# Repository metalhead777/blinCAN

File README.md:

# blinCAN
A 24 channel LED driver module with CAN bus interface and Arduino-compatible microcontroller. 

*blinCAN v0.1 2018 top*

*blinCAN v0.1 2018 bottom*

## Function description

The blinCAN is based on a multi-channel power LED driver module developed for the [Desert Eyes project](http://deserteyes.net/). 
It is matched to a small-scale construction prototype dome, which served to test construction and lighting patterns for the full-scale dome. 

This module is built around a TLC5947 PWM LED driver IC, which is connected to an ATmega328 microcontroller. 
For communication, a MCP2551 CAN transceiver and a MCP2515 CAN controller with SPI interface to the microcontroller are utilized. 
A FT232R USB to UART interface has been added to allow programming via USB, once a bootloader is flashed onto the microcontroller. 
For ambient air temperature sensing, a LM35 temperature sensor has been placed near the LED driver IC. 
A DIP switch is used to set a hardware-level address on each device, which also gets indicated by corresponding LEDs.
For easier connection of an already wired LED harness, 25-pin SUB-D connectors are used on the output. 

On the small-scale construction prototype dome, a Raspberry Pi with a CAN bus HAT was used as a host to centrally generate and send lighting patterns to six blinCAN modules via the CAN bus. 
Each blinCAN module had a unique address within the CAN bus, and every LED on the dome was purposely connected to a predefined module output. 
This way, every LED on the dome's shell was distinctly addressable in 3D space. 
An underlying look-up-table in the host's software was used to map each pattern lighting point to an LED. 

### Current stage of development
Currently the blinCAN is in early development state in version 0.1. 
This means, that the hardware is tested and working on a small prototype scale production. 
Long-term testing (temperature, vibration, EMI) has not been performed yet. 
In this state the blinCAN is fit to be used for embedded systems and small-scale lighting projects. 
Any large-scale production is not encouraged, since additional optimization in the hardware layout needs to be done for that. 

A few prototypes have been built and successfully tested prior to releasing this repository. 

### Device commissioning description

#### Device connection

#### Device power requirements

### Device programming

After assembly, the device can only be programmed using an ICSP in-circuit-programmer.
The connector with the reference **P103** serves as ICSP header.
The square pad is ICSP Pin 1 (MISO).

*P103 ICSP header pin connection*

The blinCAN firmware can be flashed directly to the ATmega328P-AU using an In-Series Programmer (ISP).
The reset-button needs to be pressed during microcontroller flashing

For editing the blinCAN firmware or testing any other Arduino-compatible code, the Arduino bootlader needs to be flashed first to the ATmega328P-AU used for the blinCAN.
A tutorial on flashing the Arduino bootloader can be found [here](https://www.arduino.cc/en/tutorial/arduinoISP).
Use the following settings under "Tools" in the Arduino IDE, if you use another Arduino as a flashing device (ISP):

| Parameter | Value          |
| --------- |:--------------:|
| Board     | "Arduino Nano" |
| Processor | "ATmega328P"   |

After flashing the Arduino bootloader, any further programming can be done using the USB type B connector (**P104**) on the blinCAN.

#### Windows

#### Linux

#### MacOS

#### List of successfully tested programming adaptors

### Device communication reference

#### Internal

#### External

#### Addressing scheme

## Currently known bugs and issues
- Reset-button needs to be pressed during microcontroller flashing
- The TLC5947 has a thermal pad, which makes it the only component not solderable by purely using a soldering iron. Using a heatgun to heat the pad from the bottom side, applying solder and then placing the TLC5947 onto it has been done successfully for the prototypes.

## Planned future changes and improvements
- Add Bill of Materials (BOM) for all non-KiCAD users
- Clean up trace routing around TLC5947
- Increase number of hardware address bits
- Change LED output voltage to board input voltage instead of fix 5 V
- Add polyfuse for input overcurrent protection
- Add additional mounting points for Raspberry Pi (host system)

## Open source hardware and software used in this project

### KiCAD

- [KiCAD website](http://kicad.org/)
- Licensed under [GPL Version 3](https://www.gnu.org/licenses/gpl-3.0.html)

### Arduino nano Rev. 3

- [Arduino website](https://www.arduino.cc/)
- [Arduino nano Rev. 3 schematic](https://arduino.cc/en/uploads/Main/Arduino_Nano-Rev3.2-SCH.pdf)
- Licensed under [CC BY-SA 3.0](https://creativecommons.org/licenses/by-sa/3.0/)

### Arduino SparkFun CAN-Bus Shield Rev. 13

- [SparkFun website](https://www.sparkfun.com/)
- [SparkFun CAN-Bus Shield on GitHub](https://github.com/sparkfun/CAN-Bus_Shield/tree/V_H1.3_L5.0.0)
- [SparkFun CAN-Bus Shield Rev. 13 schematic](http://cdn.sparkfun.com/datasheets/Dev/Arduino/Shields/SparkFun_CAN-Bus_Shield_v13a.pdf)
- Licensed under [CC BY-SA 4.0](https://creativecommons.org/licenses/by-sa/4.0/)

## Active contributors to this project

### Firmware programmers

### Library programmers

## License information

This project is open source and licensed under [Creative Commons Attribution Share Alike 4.0](https://creativecommons.org/licenses/by-sa/4.0/).

Please refer to [License.md](License.md) for the full legal text. 
Thanks to [idleberg on GitHub](https://github.com/idleberg/Creative-Commons-Markdown) for the Markdown format. 

The project is distributed as-is. No warranty is given.

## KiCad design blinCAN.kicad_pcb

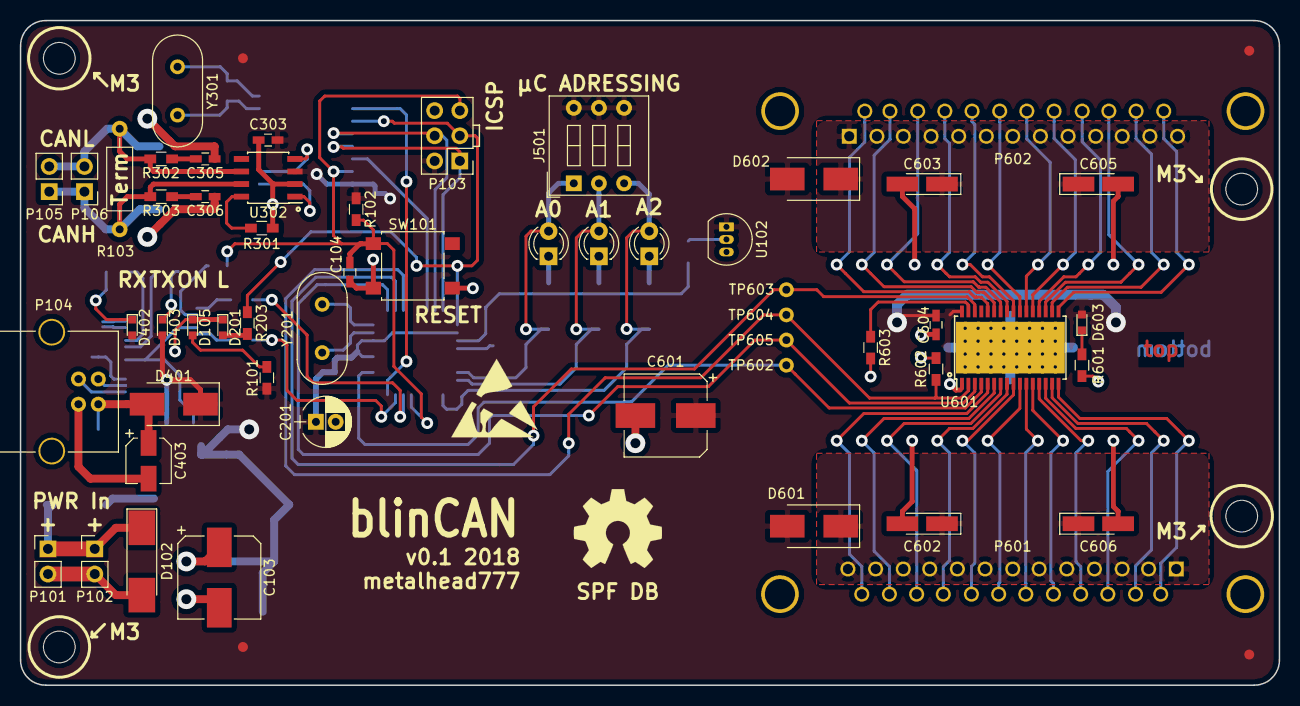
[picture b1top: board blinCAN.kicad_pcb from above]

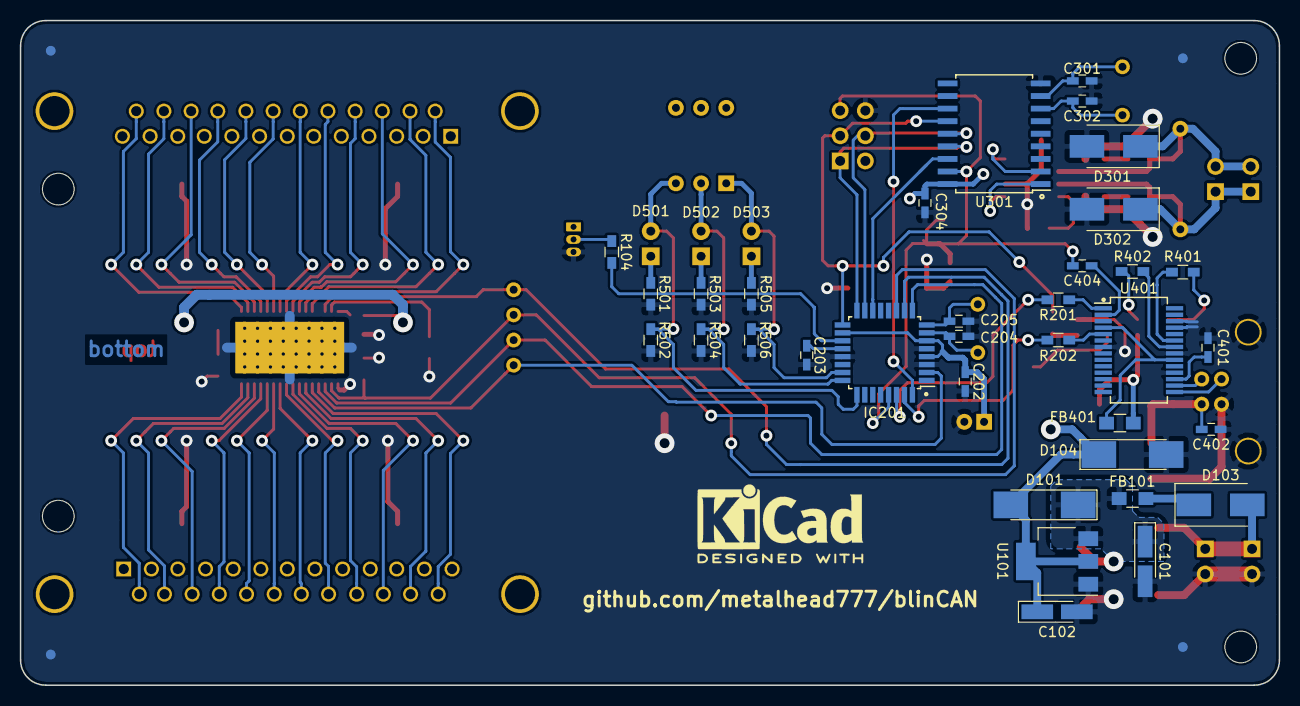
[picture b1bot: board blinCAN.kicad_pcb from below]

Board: 2 copper layers, 127.1 x 67.1 mm, 88 parts (34 on the bottom side), 79 nets.

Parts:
C101, C102, C602, C603, C605, C606: Tantal 10u/16V; CP_Tantalum_Case-A_EIA-3216-18_Hand
C103: 330u/25V; CP_Elec_8x10.5
C104, C202, C203, C303, C304, C401, C402, C404, C604: 100N; C_0603_HandSoldering
C201: 4.7u/16V; CP_Radial_D5.0mm_P2.00mm
C204, C205, C301, C302: 22P; C_0603_HandSoldering
C305, C306: 560p; C_0603_HandSoldering
C403: 4.7u/16V; CP_Elec_4x5.7
C601: 330u/16V; CP_Elec_8x10.5
D101, D102, D104: 1N 4001 SMD; D_MELF_Handsoldering
D103, D401, D601, D602: MBRS 240 SMD; D_SMB_Handsoldering
D105: LED Blue; LED_0603
D201: LED Orange; LED_0603
D301, D302: P6SMB 27A SMD; D_SMB_Handsoldering
D402: LED Red; LED_0603
D403, D603: LED Green; LED_0603
D501, D502, D503: LED Orange; LED_D3.0mm
FB101, FB401: EMI suppression Filter 30 Ohms; L_0805_HandSoldering
IC201: ATMEGA328P-AU; TQFP-32_7x7mm_Pitch0.8mm
J501: Conn_Address; SW_DIP_x3_W7.62mm_Slide
P101, P102: Conn_PWR_IN; Pin_Header_Straight_1x02_Pitch2.54mm
P103: CONN_ICSP; Pin_Header_Straight_2x03_Pitch2.54mm
P104: USB B; USB_B
P105, P106: Conn_CAN; Pin_Header_Straight_1x02_Pitch2.54mm
P601, P602: D-SUB 25; DB25FC
R101, R203, R401, R402: 330; R_0603_HandSoldering
R102, R104, R201, R202: 1k; R_0603_HandSoldering
R103: 120; R_Axial_DIN0207_L6.3mm_D2.5mm_P10.16mm_Horizontal
R301: 4k7; R_0603_HandSoldering
R302, R303: 100; R_0603_HandSoldering
R501, R503, R505: 130; R_0603_HandSoldering
R502, R504, R506: 10k; R_0603_HandSoldering
R601: 470; R_0603_HandSoldering
R602: 10K; R_0603_HandSoldering
R603: 3K3; R_0603_HandSoldering
SW101: Reset; SW_SPST_B3S-1000
TP602: TEST_DIN; Measurement_Point_Round-TH_Small
TP603: TEST_LAT; Measurement_Point_Round-TH_Small
TP604: TEST_OE; Measurement_Point_Round-TH_Small
TP605: TEST_CLK; Measurement_Point_Round-TH_Small
U101: LD1117S50TR_SOT223; SOT-223-3_TabPin2
U102: LM35DZ; TO-92_Inline_Narrow_Oval
U301: MCP2515-I/SO; SOIC-18W_7.5x11.6mm_Pitch1.27mm
U302: MCP2551-I/SN; SOIC-8_3.9x4.9mm_Pitch1.27mm
U401: FT232R; SSOP-28_5.3x10.2mm_Pitch0.65mm
U601: TLC5947; HTSSOP-32_6.1x11mm_Pitch0.65mm_ThermalPad
Y201, Y301: 16 MHz; Crystal_HC49-U_Vertical

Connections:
0-: P601.25, U601.5
1-: P601.24, U601.6
2-: P601.23, U601.7
3-: P601.22, U601.8
4-: P601.21, U601.9
5-: P601.20, U601.10
6-: P601.19, U601.11
7-: P601.18, U601.12
8-: P601.17, U601.13
9-: P601.16, U601.14
10-: P601.15, U601.15
11-: P601.14, U601.16
12-: P602.25, U601.17
13-: P602.24, U601.18
14-: P602.23, U601.19
15-: P602.22, U601.20
16-: P602.21, U601.21
17-: P602.20, U601.22
18-: P602.19, U601.23
19-: P602.18, U601.24
20-: P602.17, U601.25
21-: P602.16, U601.26
22-: P602.15, U601.27
23-: P602.14, U601.28
+5V: C102.1, C201.1, C202.1, C303.1, C304.1, C601.1, C604.2, D101.2, D104.1, D401.1, D402.2, D403.2, D601.2, D602.2, D603.2, FB401.2, IC201.4, IC201.6, IC201.18, J501.4, J501.5, J501.6, P103.2, R101.1, R102.1, U101.2, U102.1, U301.18, U302.3, U601.32
+12V: C101.1, C103.1, D101.1, FB101.1, U101.3
/Addressing_Switch/Addr0: D503.2, IC201.23, J501.1, R506.2
/Addressing_Switch/Addr1: D502.2, IC201.24, J501.2, R504.2
/Addressing_Switch/Addr2: D501.2, IC201.25, J501.3, R502.2
/CAN_Bus_Driver_Controller//CAN_INT: IC201.32, U301.12
/CAN_Bus_Driver_Controller//CS_CAN: IC201.14, U301.16
/CAN_Bus_Driver_Controller//Reset_CAN: C104.1, C404.2, IC201.29, P103.5, R102.2, SW101.1, U301.17
/CAN_Bus_Driver_Controller/CAN_+: D302.1, P105.1, P106.1, R103.1, R303.1, U302.7
/CAN_Bus_Driver_Controller/CAN_-: D301.1, P105.2, P106.2, R103.2, R302.1, U302.6
/CAN_Bus_Driver_Controller/MISO_CAN: IC201.16, P103.1, U301.15
/CAN_Bus_Driver_Controller/MOSI_CAN: IC201.15, P103.4, U301.14
/Microcontroller/ADC6/A6: IC201.19, R104.2
/Microcontroller/AREF: C203.1, IC201.20
/Microcontroller/PB5/D13/SCKuC: IC201.17, P103.3, R203.1, U301.13
/Microcontroller/PD0/D0/RXuC: R201.1, U401.1
/Microcontroller/PD1/D1/TXuC: R202.1, U401.5
/OE: IC201.11, R602.1, TP604.1, U601.2
/USB_RS232_IC/D+_USB: P104.3, U401.15
/USB_RS232_IC/D-_USB: P104.2, U401.16
/USB_RS232_IC/VCC_USB_Conn: C402.1, C403.1, D401.2, P104.1
CLK: IC201.9, TP605.1, U601.3
DIN: IC201.2, TP602.1, U601.4
GND: C101.2, C102.2, C103.2, C104.2, C201.2, C202.2, C203.2, C204.2, C205.2, C301.2, C302.2, C303.2, C304.2, C305.2, C306.2, C401.2, C402.2, C403.2, C601.2, C602.2, C603.2, C604.1, C605.2, C606.2, D102.2, D104.2, D105.1, D201.1, D301.2, D302.2, IC201.3, IC201.5, IC201.21, P101.2, P102.2, P103.6, P104.4, P104.5, R301.2, R501.1, R502.1, R503.1, R504.1, R505.1, R506.1, R601.2, R602.2, R603.2, SW101.2, U101.1, U102.3, U301.9, U302.2, U401.7, U401.18, U401.21, U401.25, U401.26, U601.1, U601.33
LAT: IC201.10, TP603.1, U601.30
unnamed: C204.1, IC201.7, Y201.1
unnamed: C205.1, IC201.8, Y201.2
unnamed: C301.1, U301.8, Y301.1
unnamed: C302.1, U301.7, Y301.2
unnamed: C305.1, R302.2
unnamed: C306.1, R303.2
unnamed: C401.1, U401.17
unnamed: C404.1, U401.2
unnamed: D102.1, D103.2, P101.1, P102.1
unnamed: D103.1, FB101.2
unnamed: D105.2, R101.2
unnamed: D201.2, R203.2
unnamed: D402.1, R401.1
unnamed: D403.1, R402.1
unnamed: D501.1, R501.2
unnamed: D502.1, R503.2
unnamed: D503.1, R505.2
unnamed: D603.1, R601.1
unnamed: FB401.1, U401.4, U401.20
unnamed: IC201.30, R201.2
unnamed: IC201.31, R202.2
unnamed: R104.1, U102.2
unnamed: R301.1, U302.8
unnamed: R401.2, U401.23
unnamed: R402.2, U401.22
unnamed: R603.1, U601.31
unnamed: U301.1, U302.1
unnamed: U301.2, U302.4
V+_LED_A: C602.1, C606.1, D601.1, P601.1, P601.2, P601.3, P601.4, P601.5, P601.6, P601.7, P601.8, P601.9, P601.10, P601.11, P601.12, P601.13
V+_LED_B: C603.1, C605.1, D602.1, P602.1, P602.2, P602.3, P602.4, P602.5, P602.6, P602.7, P602.8, P602.9, P602.10, P602.11, P602.12, P602.13

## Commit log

2017-10-31 Update README.md
    Add headlines
2017-10-31 Update README.md
    Add some future improvements. Add known Reset bug during programming
2017-11-01 Initial commit: Add KiCAD project files, library files and footprints
2017-11-01 Comment .lib to not interfere with KiCAD.
2017-11-01 Add KiCAD libraries.
2017-11-07 Add symbols to PCB.
2017-11-07 Add mounting holes. Moved symbols.
2017-11-07 Move symbols.
2017-11-07 Add 3D model for TLC5947 to PCB.
2017-11-07 Update README.md
    Remove info about DIP switch from future changes and improvements,since it has been implemented.
2017-11-16 Update README.md
    Add note about future work.
2017-11-28 Update README.md
    Add information for function description and multiple small corrections.
2018-01-21 Fix some silkscreen misplacements.
2018-01-21 Add fiducial marks
2018-01-21 Update date on schematics and PCB drawing
2018-01-21 Update README.md
    Add license information.
2018-01-21 Add GERBER files
2018-01-21 Add license file.
2018-01-21 Add note about license file
2018-01-21 Update README.md
    provide local link to license file
2018-01-21 Update README.md
    Add note about warranty.
2019-12-12 Add note about adding BOM in the future. Clean up third-party open source hardware and software used.
2019-12-12 Add PCB renders of current version v0.1.
2019-12-12 Add pictures to README.md.
2019-12-12 Add ICSP header picture.
2019-12-12 Add device programming instructions to README.md.
2021-11-10 Update README.md
    https://forum.kicad.info/t/warning-avoid-all-links-to-kicad-pcb-org-use-kicad-org/31521
